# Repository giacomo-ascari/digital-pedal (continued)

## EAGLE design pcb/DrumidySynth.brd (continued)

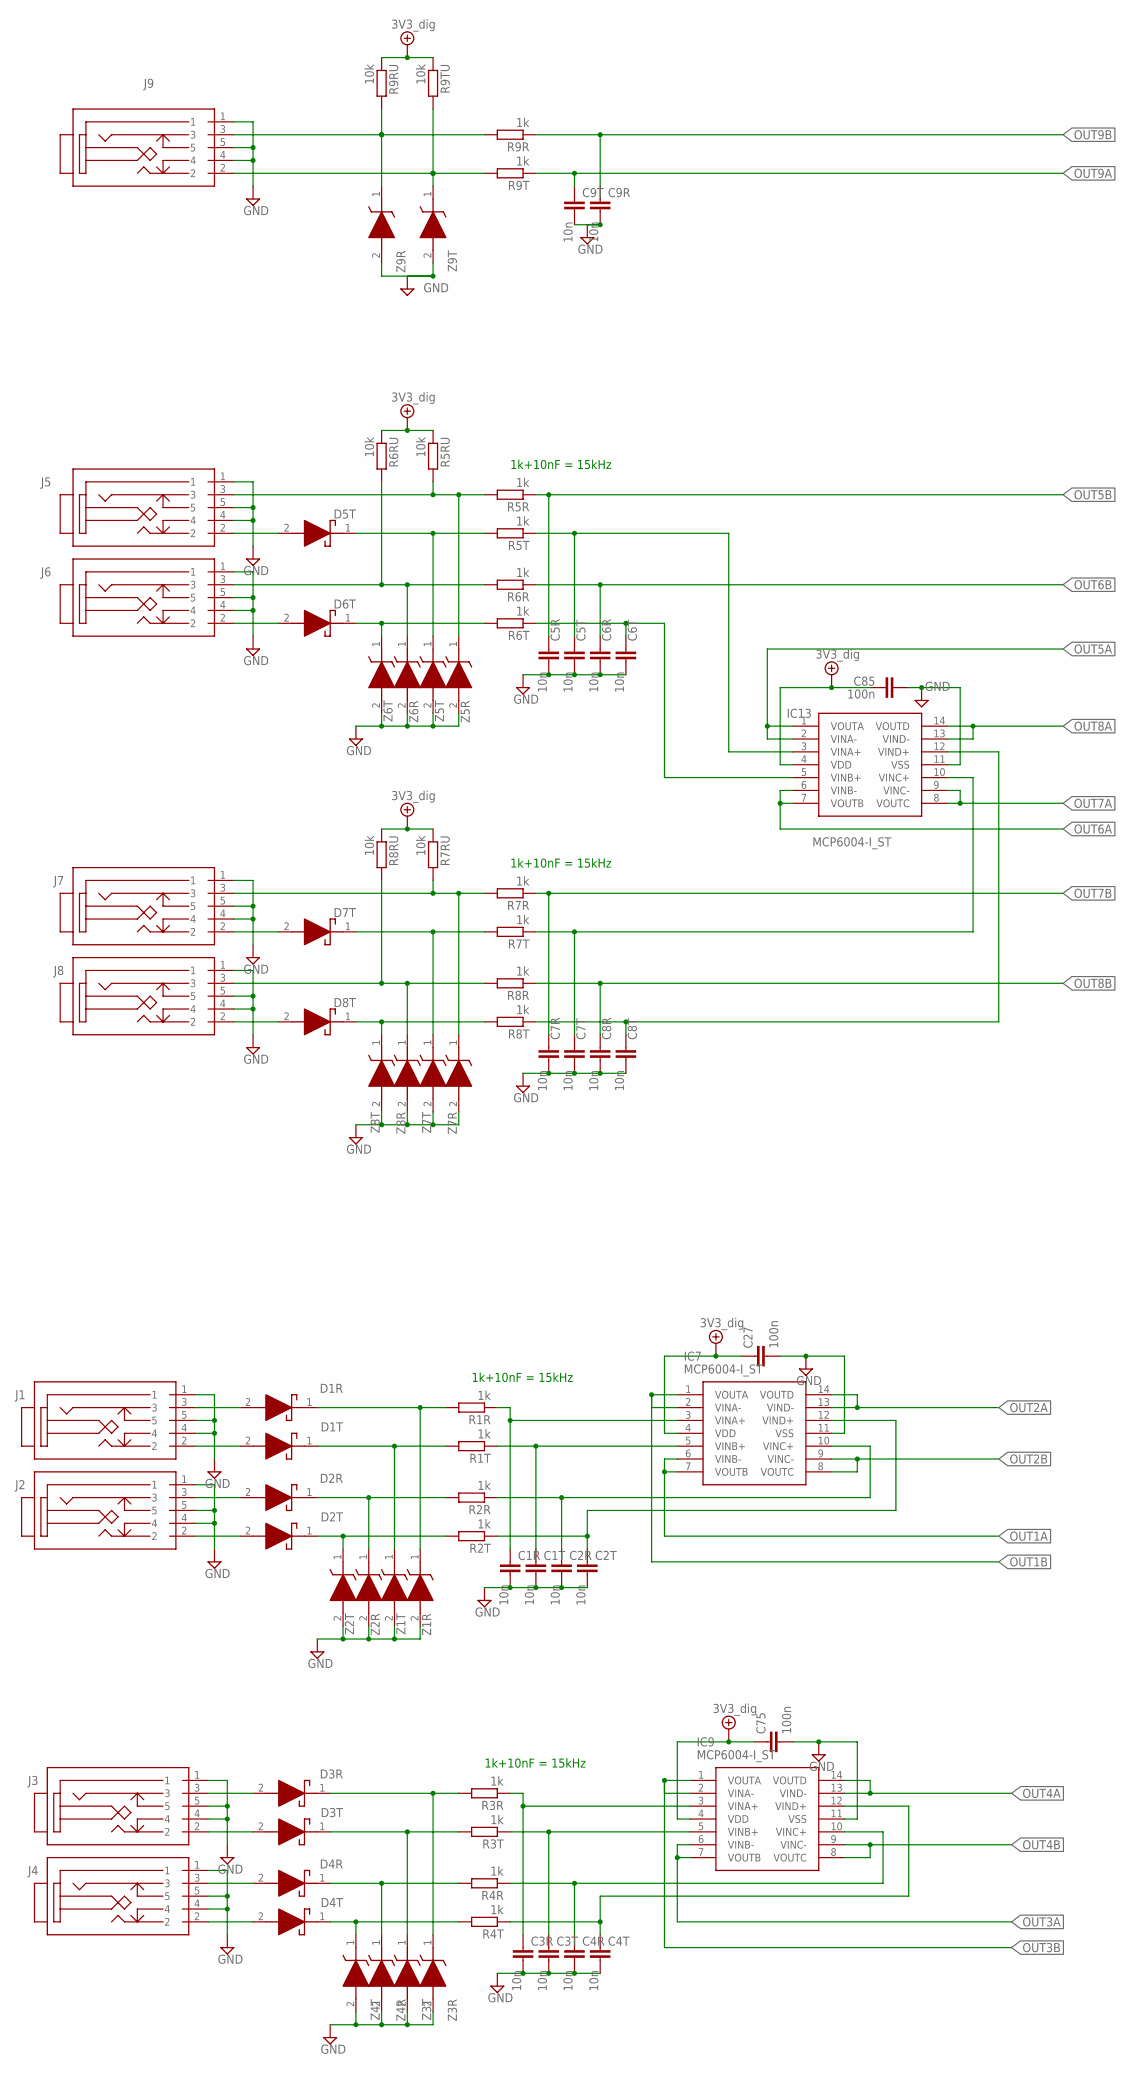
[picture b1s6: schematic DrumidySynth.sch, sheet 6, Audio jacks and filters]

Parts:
C1R, C1T, C2R, C2T, C3R, C3T, C4R, C4T, C5R, C5T, C6R, C6T, C7R, C7T, C8R, C8T, C9R, C9T: 10n; C0603K
C27, C75, C85: 100n; C0805
D1R, D1T, D2R, D2T, D3R, D3T, D4R, D4T, D5T, D6T, D7T, D8T: BAT54J,115; SODFL2512X80N
IC7, IC9, IC13: MCP6004-I_ST; SOP65P640X120-14N
J1, J2, J3, J4, J5, J6, J7, J8, J9: 35RAPC2AVN4
R1R, R1T, R2R, R2T, R3R, R3T, R4R, R4T, R5R, R5T, R6R, R6T, R7R, R7T, R8R, R8T, R9R, R9T: 1k; R0603
R5RU, R6RU, R7RU, R8RU, R9RU, R9TU: 10k; R0603
Z1R, Z1T, Z2R, Z2T, Z3R, Z3T, Z4R, Z4T, Z5R, Z5T, Z6R, Z6T, Z7R, Z7T, Z8R, Z8T, Z9R, Z9T: MM3Z3V3T1G; SOD2512X110N

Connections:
3V3D: C27.1, C75.1, C85.1, IC7.4 (VDD), IC9.4 (VDD), IC13.4 (VDD), R5RU.1, R6RU.1, R7RU.1, R8RU.1, R9RU.1, R9TU.1; also elsewhere on the board
GND: C1R.2, C1T.2, C2R.2, C2T.2, C3R.2, C3T.2, C4R.2, C4T.2, C5R.2, C5T.2, C6R.2, C6T.2, C7R.2, C7T.2, C8R.2, C8T.2, C9R.2, C9T.2, C27.2, C75.2, C85.2, IC7.11 (VSS), IC9.11 (VSS), IC13.11 (VSS), J1.1, J1.4, J1.5, J2.1, J2.4, J2.5, J3.1, J3.4, J3.5, J4.1, J4.4, J4.5, J5.1, J5.4, J5.5, J6.1, J6.4, J6.5, J7.1, J7.4, J7.5, J8.1, J8.4, J8.5, J9.1, J9.4, J9.5, Z1R.2 (A), Z1T.2 (A), Z2R.2 (A), Z2T.2 (A), Z3R.2 (A), Z3T.2 (A), Z4R.2 (A), Z4T.2 (A), Z5R.2 (A), Z5T.2 (A), Z6R.2 (A), Z6T.2 (A), Z7R.2 (A), Z7T.2 (A), Z8R.2 (A), Z8T.2 (A), Z9R.2 (A), Z9T.2 (A); also elsewhere on the board
IN0A: C1R.1, IC7.3 (VINA+), R1R.1
IN0A2: C3R.1, IC9.3 (VINA+), R3R.1
IN0B: C1T.1, IC7.5 (VINB+), R1T.1
IN0B1: C7T.1, IC13.10 (VINC+), R7T.1
IN0B2: C3T.1, IC9.5 (VINB+), R3T.1
IN0B4: C5T.1, IC13.3 (VINA+), R5T.1
IN1A: C2R.1, IC7.10 (VINC+), R2R.1
IN1A2: C4R.1, IC9.10 (VINC+), R4R.1
IN1B: C2T.1, IC7.12 (VIND+), R2T.1
IN1B1: C8T.1, IC13.12 (VIND+), R8T.1
IN1B2: C4T.1, IC9.12 (VIND+), R4T.1
unnamed: J7.3, R7R.2, R7RU.2, Z7R.1 (K)
unnamed: D7T.2 (A), J7.2
unnamed: J8.3, R8R.2, R8RU.2, Z8R.1 (K)
unnamed: D8T.2 (A), J8.2
unnamed: D1R.2 (A), J1.3
unnamed: D1T.2 (A), J1.2
unnamed: D2R.2 (A), J2.3
unnamed: D2T.2 (A), J2.2
unnamed: D1R.1 (K), R1R.2, Z1R.1 (K)
unnamed: D1T.1 (K), R1T.2, Z1T.1 (K)
unnamed: D2R.1 (K), R2R.2, Z2R.1 (K)
unnamed: D2T.1 (K), R2T.2, Z2T.1 (K)
unnamed: D7T.1 (K), R7T.2, Z7T.1 (K)
unnamed: D8T.1 (K), R8T.2, Z8T.1 (K)
unnamed: D3R.2 (A), J3.3
unnamed: D3T.2 (A), J3.2
unnamed: D4R.2 (A), J4.3
unnamed: D4T.2 (A), J4.2
unnamed: D3R.1 (K), R3R.2, Z3R.1 (K)
unnamed: D3T.1 (K), R3T.2, Z3T.1 (K)
unnamed: D4R.1 (K), R4R.2, Z4R.1 (K)
unnamed: D4T.1 (K), R4T.2, Z4T.1 (K)
unnamed: J9.3, R9R.2, R9RU.2, Z9R.1 (K)
unnamed: C6T.1, IC13.5 (VINB+), R6T.1
unnamed: J9.2, R9T.2, R9TU.2, Z9T.1 (K)
unnamed: J5.3, R5R.2, R5RU.2, Z5R.1 (K)
unnamed: D5T.2 (A), J5.2
unnamed: J6.3, R6R.2, R6RU.2, Z6R.1 (K)
unnamed: D6T.2 (A), J6.2
unnamed: D5T.1 (K), R5T.2, Z5T.1 (K)
unnamed: D6T.1 (K), R6T.2, Z6T.1 (K)
OUT1A: IC7.6 (VINB-), IC7.7 (VOUTB); also elsewhere on the board
OUT1B: IC7.1 (VOUTA), IC7.2 (VINA-); also elsewhere on the board
OUT2A: IC7.13 (VIND-), IC7.14 (VOUTD); also elsewhere on the board
OUT2B: IC7.8 (VOUTC), IC7.9 (VINC-); also elsewhere on the board
OUT3A: IC9.6 (VINB-), IC9.7 (VOUTB); also elsewhere on the board
OUT3B: IC9.1 (VOUTA), IC9.2 (VINA-); also elsewhere on the board
OUT4A: IC9.13 (VIND-), IC9.14 (VOUTD); also elsewhere on the board
OUT4B: IC9.8 (VOUTC), IC9.9 (VINC-); also elsewhere on the board
OUT5A: IC13.1 (VOUTA), IC13.2 (VINA-); also elsewhere on the board
OUT5B: C5R.1, R5R.1; also elsewhere on the board
OUT6A: IC13.6 (VINB-), IC13.7 (VOUTB); also elsewhere on the board
OUT6B: C6R.1, R6R.1; also elsewhere on the board
OUT7A: IC13.8 (VOUTC), IC13.9 (VINC-); also elsewhere on the board
OUT7B: C7R.1, R7R.1; also elsewhere on the board
OUT8A: IC13.13 (VIND-), IC13.14 (VOUTD); also elsewhere on the board
OUT8B: C8R.1, R8R.1; also elsewhere on the board
OUT9A: C9T.1, R9T.1; also elsewhere on the board
OUT9B: C9R.1, R9R.1; also elsewhere on the board

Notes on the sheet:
1k+10nF = 15kHz

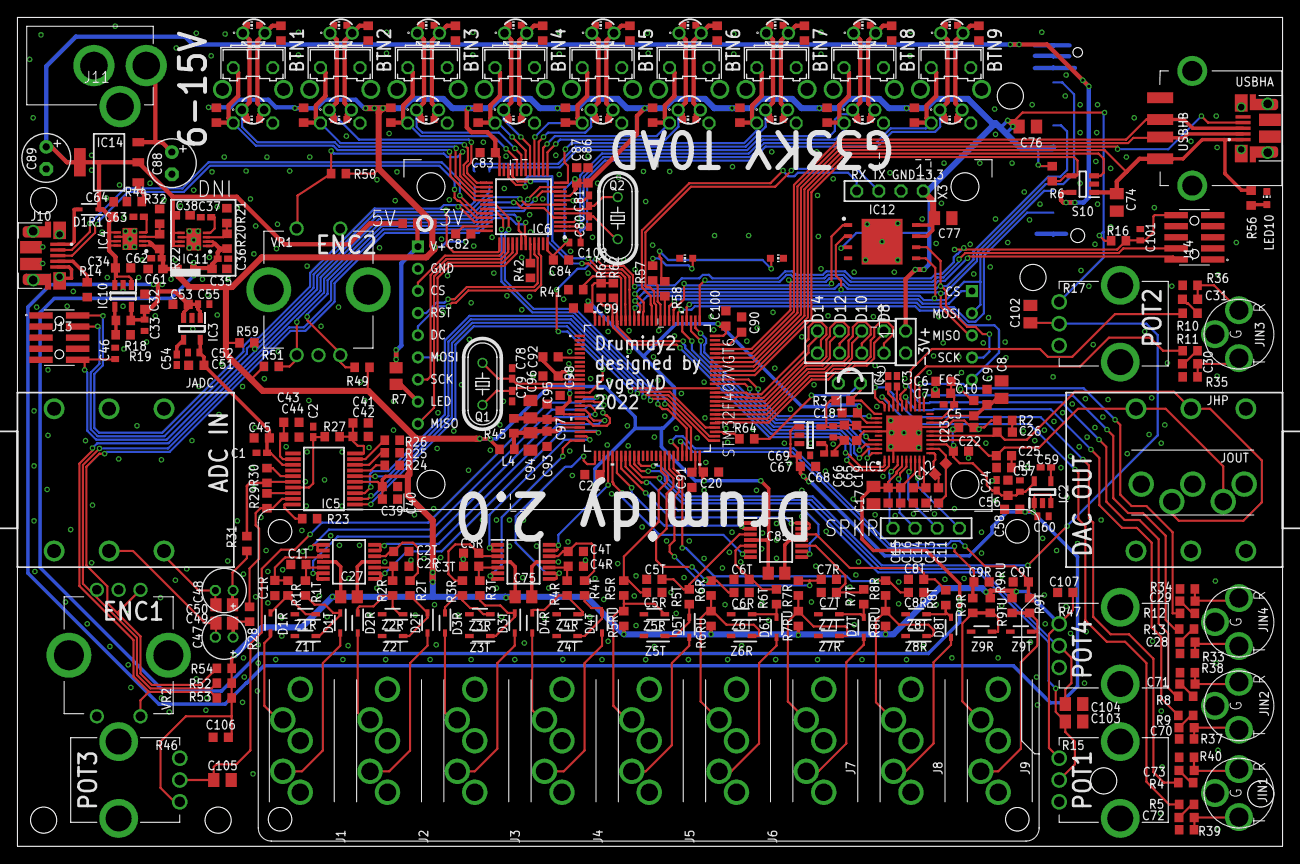
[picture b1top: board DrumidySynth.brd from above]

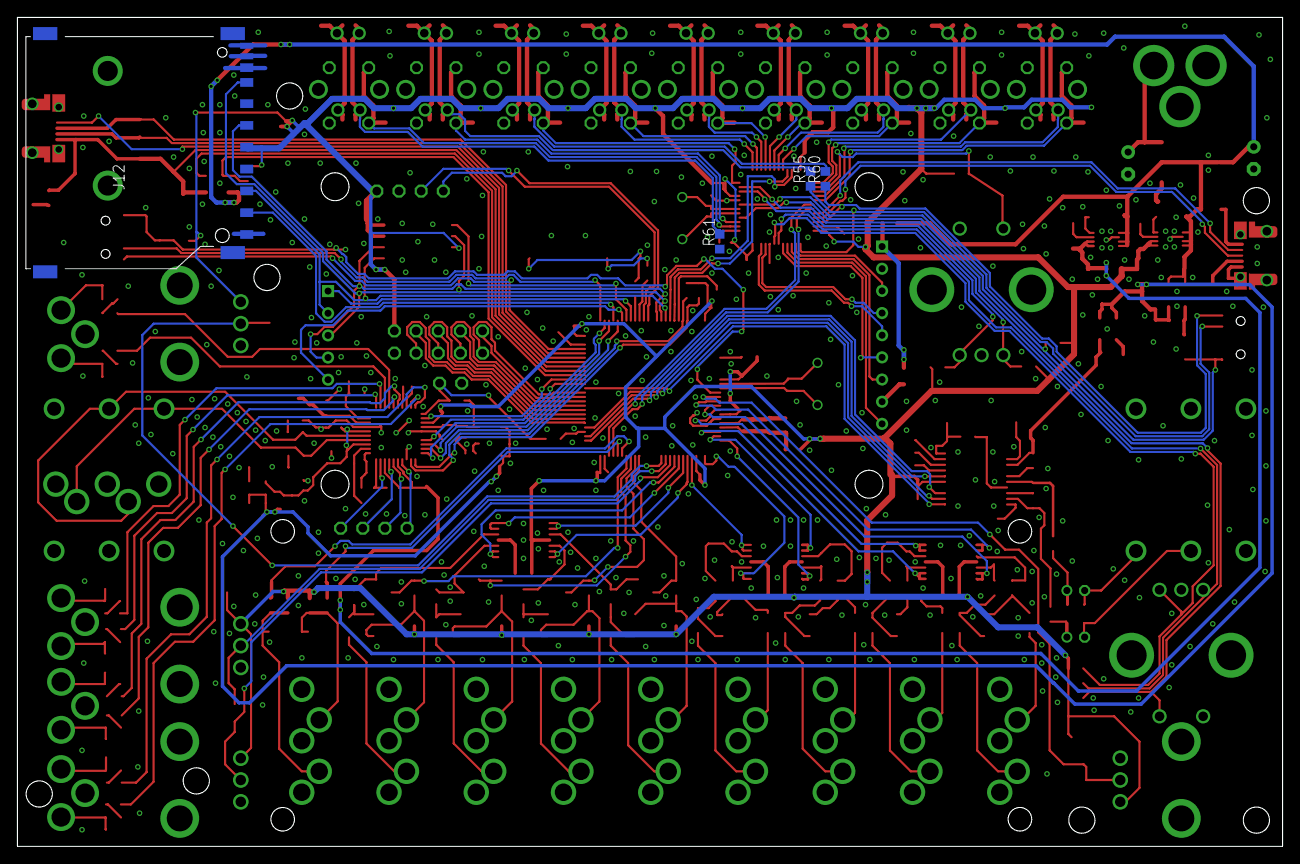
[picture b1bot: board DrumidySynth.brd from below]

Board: 2 copper layers, 145.0 x 95.0 mm, 363 parts (4 on the bottom side), 244 nets.

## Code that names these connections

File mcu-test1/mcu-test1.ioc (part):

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Mcu.Name=STM32F407V(E-G)Tx
Mcu.Package=LQFP100
Mcu.UserName=STM32F407VGTx
PA0-WKUP.GPIOParameters=GPIO_Label
PA0-WKUP.GPIO_Label=Btn0
PA0-WKUP.Signal=GPIO_Input
PA1.GPIOParameters=GPIO_Label
PA1.GPIO_Label=EPD_RST
PA1.Signal=GPIO_Output
PA11.GPIOParameters=GPIO_Speed
PA11.GPIO_Speed=GPIO_SPEED_FREQ_LOW
PA11.Mode=Host_Only
PA11.Signal=USB_OTG_FS_DM
PA12.GPIOParameters=GPIO_Speed
PA12.GPIO_Speed=GPIO_SPEED_FREQ_LOW
PA12.Mode=Host_Only
PA12.Signal=USB_OTG_FS_DP
PA13.Mode=Serial_Wire
PA13.Signal=SYS_JTMS-SWDIO
PA14.Mode=Serial_Wire
PA14.Signal=SYS_JTCK-SWCLK
PA2.GPIOParameters=GPIO_Label
PA2.GPIO_Label=EPD_DC
PA2.Signal=GPIO_Output
PA3.GPIOParameters=GPIO_Label
PA3.GPIO_Label=EPD_BUSY
PA3.Signal=GPIO_Input
PA4.GPIOParameters=GPIO_Speed
PA4.GPIO_Speed=GPIO_SPEED_FREQ_MEDIUM
PA4.Mode=Half_Duplex_Master
PA4.Signal=I2S3_WS
PA5.Mode=Simplex_Bidirectional_Master
PA5.Signal=SPI1_SCK
PA6.GPIOParameters=PinState,GPIO_Label
PA6.GPIO_Label=EPD_CS
PA6.PinState=GPIO_PIN_RESET
PA6.Signal=GPIO_Output
PA7.Mode=Simplex_Bidirectional_Master
PA7.Signal=SPI1_MOSI
PA9.Mode=Activate_VBUS
PA9.Signal=USB_OTG_FS_VBUS
PB11.GPIOParameters=GPIO_PuPd,GPIO_Label
PB11.GPIO_Label=Btn3
PB11.GPIO_PuPd=GPIO_PULLUP
PB11.Signal=GPIO_Input
PB12.GPIOParameters=GPIO_Speed
PB12.GPIO_Speed=GPIO_SPEED_FREQ_MEDIUM
PB12.Mode=Half_Duplex_Master
PB12.Signal=I2S2_WS
PB13.GPIOParameters=GPIO_Speed
PB13.GPIO_Speed=GPIO_SPEED_FREQ_MEDIUM
PB13.Mode=Half_Duplex_Master
PB13.Signal=I2S2_CK
PB14.GPIOParameters=GPIO_PuPd,GPIO_Label
PB14.GPIO_Label=Btn2
PB14.GPIO_PuPd=GPIO_PULLUP
PB14.Signal=GPIO_Input
PB15.GPIOParameters=GPIO_Speed
PB15.GPIO_Speed=GPIO_SPEED_FREQ_MEDIUM
PB15.Mode=Half_Duplex_Master
PB15.Signal=I2S2_SD
PB6.Mode=I2C
PB6.Signal=I2C1_SCL
PB9.Mode=I2C
PB9.Signal=I2C1_SDA
PC0.GPIOParameters=PinState,GPIO_Label
PC0.GPIO_Label=OtgPower
PC0.PinState=GPIO_PIN_RESET
PC0.Signal=GPIO_Output
PC10.GPIOParameters=GPIO_Speed
PC10.GPIO_Speed=GPIO_SPEED_FREQ_MEDIUM
PC10.Mode=Half_Duplex_Master
PC10.Signal=I2S3_CK
PC12.GPIOParameters=GPIO_Speed
PC12.GPIO_Speed=GPIO_SPEED_FREQ_MEDIUM
PC12.Mode=Half_Duplex_Master
PC12.Signal=I2S3_SD
PC2.GPIOParameters=GPIO_Label
PC2.GPIO_Label=EncB
PC2.Signal=GPIO_Input
PC3.GPIOParameters=GPIO_Label
PC3.GPIO_Label=EncA
PC3.Signal=GPIO_Input
PC6.GPIOParameters=GPIO_Speed
PC6.GPIO_Speed=GPIO_SPEED_FREQ_MEDIUM
PC6.Mode=Master_Clock_Activated
PC6.Signal=I2S2_MCK
PC7.GPIOParameters=GPIO_Speed
PC7.GPIO_Speed=GPIO_SPEED_FREQ_MEDIUM
PC7.Mode=Master_Clock_Activated
PC7.Signal=I2S3_MCK
PD12.GPIOParameters=GPIO_Label
PD12.GPIO_Label=Led1
PD12.Signal=GPIO_Output
PD13.GPIOParameters=GPIO_Label
PD13.GPIO_Label=Led2
PD13.Signal=GPIO_Output
PD14.GPIOParameters=GPIO_Label
PD14.GPIO_Label=Led3
PD14.Signal=GPIO_Output
PD15.GPIOParameters=PinState,GPIO_Label
PD15.GPIO_Label=Led4
PD15.PinState=GPIO_PIN_RESET
PD15.Signal=GPIO_Output
PD4.GPIOParameters=PinState,GPIO_Label
PD4.GPIO_Label=AudioPower
PD4.PinState=GPIO_PIN_SET
PD4.Signal=GPIO_Output
PD8.GPIOParameters=GPIO_PuPd,GPIO_Label
PD8.GPIO_Label=Btn1
PD8.GPIO_PuPd=GPIO_PULLUP
PD8.Signal=GPIO_Input
PH0-OSC_IN.Mode=HSE-External-Oscillator
PH0-OSC_IN.Signal=RCC_OSC_IN
PH1-OSC_OUT.Mode=HSE-External-Oscillator
PH1-OSC_OUT.Signal=RCC_OSC_OUT
RCC.HSE_VALUE=8000000
RCC.SYSCLKFreq_VALUE=168000000
RCC.SYSCLKSource=RCC_SYSCLKSOURCE_PLLCLK
board=custom

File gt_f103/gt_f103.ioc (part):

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Mcu.Name=STM32F103C(8-B)Tx
Mcu.Package=LQFP48
Mcu.UserName=STM32F103C8Tx
PA0-WKUP.GPIOParameters=GPIO_Label
PA0-WKUP.GPIO_Label=ENC2B
PA0-WKUP.Signal=GPIO_Input
PA1.GPIOParameters=GPIO_Label
PA1.GPIO_Label=ENC2A
PA1.Signal=GPIO_Input
PA13.Mode=Serial_Wire
PA13.Signal=SYS_JTMS-SWDIO
PA14.Mode=Serial_Wire
PA14.Signal=SYS_JTCK-SWCLK
PA15.GPIOParameters=GPIO_Label
PA15.GPIO_Label=LCD_CS
PA15.Signal=GPIO_Output
PA3.GPIOParameters=GPIO_Label
PA3.GPIO_Label=LD6
PA3.Signal=GPIO_Output
PA4.GPIOParameters=GPIO_Label,GPIO_ModeDefaultEXTI
PA4.GPIO_Label=BTN6
PA4.GPIO_ModeDefaultEXTI=GPIO_MODE_IT_FALLING
PA4.Signal=GPXTI4
PA5.GPIOParameters=GPIO_Label
PA5.GPIO_Label=LD5
PA5.Signal=GPIO_Output
PA6.GPIOParameters=GPIO_Label,GPIO_ModeDefaultEXTI
PA6.GPIO_Label=BTN5
PA6.GPIO_ModeDefaultEXTI=GPIO_MODE_IT_FALLING
PA6.Signal=GPXTI6
PA7.GPIOParameters=GPIO_Label
PA7.GPIO_Label=LD4
PA7.Signal=GPIO_Output
PA8.GPIOParameters=GPIO_Label,GPIO_ModeDefaultEXTI
PA8.GPIO_Label=BTN1
PA8.GPIO_ModeDefaultEXTI=GPIO_MODE_IT_FALLING
PA8.Signal=GPXTI8
PB0.GPIOParameters=GPIO_Label,GPIO_ModeDefaultEXTI
PB0.GPIO_Label=BTN4
PB0.GPIO_ModeDefaultEXTI=GPIO_MODE_IT_FALLING
PB0.Signal=GPXTI0
PB1.GPIOParameters=GPIO_Label
PB1.GPIO_Label=LD3
PB1.Signal=GPIO_Output
PB10.Mode=Asynchronous
PB10.Signal=USART3_TX
PB11.Mode=Asynchronous
PB11.Signal=USART3_RX
PB12.GPIOParameters=GPIO_Label
PB12.GPIO_Label=LD2
PB12.Signal=GPIO_Output
PB13.GPIOParameters=GPIO_Label,GPIO_ModeDefaultEXTI
PB13.GPIO_Label=BTN2
PB13.GPIO_ModeDefaultEXTI=GPIO_MODE_IT_FALLING
PB13.Signal=GPXTI13
PB14.GPIOParameters=GPIO_Label,GPIO_ModeDefaultEXTI
PB14.GPIO_Label=BTN_ENC2
PB14.GPIO_ModeDefaultEXTI=GPIO_MODE_IT_FALLING
PB14.Signal=GPXTI14
PB15.GPIOParameters=GPIO_Label
PB15.GPIO_Label=LD1
PB15.Signal=GPIO_Output
PB2.GPIOParameters=GPIO_Label,GPIO_ModeDefaultEXTI
PB2.GPIO_Label=BTN3
PB2.GPIO_ModeDefaultEXTI=GPIO_MODE_IT_FALLING
PB2.Signal=GPXTI2
PB3.Mode=Full_Duplex_Master
PB3.Signal=SPI1_SCK
PB4.Mode=Full_Duplex_Master
PB4.Signal=SPI1_MISO
PB5.Mode=Full_Duplex_Master
PB5.Signal=SPI1_MOSI
PB6.GPIOParameters=GPIO_Label
PB6.GPIO_Label=ENC1B
PB6.Signal=GPIO_Input
PB7.GPIOParameters=GPIO_Label
PB7.GPIO_Label=ENC1A
PB7.Signal=GPIO_Input
PB8.GPIOParameters=GPIO_Label
PB8.GPIO_Label=LCD_RST
PB8.Signal=GPIO_Output
PB9.GPIOParameters=GPIO_Label
PB9.GPIO_Label=LCD_DC
PB9.Signal=GPIO_Output
PC15-OSC32_OUT.GPIOParameters=GPIO_Label,GPIO_ModeDefaultEXTI
PC15-OSC32_OUT.GPIO_Label=BTN_ENC1
PC15-OSC32_OUT.GPIO_ModeDefaultEXTI=GPIO_MODE_IT_FALLING
PC15-OSC32_OUT.Signal=GPXTI15
PD0-OSC_IN.Mode=HSE-External-Oscillator
PD0-OSC_IN.Signal=RCC_OSC_IN
PD1-OSC_OUT.Mode=HSE-External-Oscillator
PD1-OSC_OUT.Signal=RCC_OSC_OUT
RCC.SYSCLKFreq_VALUE=72000000
RCC.SYSCLKSource=RCC_SYSCLKSOURCE_PLLCLK
board=custom

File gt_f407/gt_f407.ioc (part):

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Mcu.Name=STM32F407V(E-G)Tx
Mcu.Package=LQFP100
Mcu.UserName=STM32F407VGTx
PA11.Mode=Host_Only
PA11.Signal=USB_OTG_FS_DM
PA12.Mode=Host_Only
PA12.Signal=USB_OTG_FS_DP
PA13.Mode=Serial_Wire
PA13.Signal=SYS_JTMS-SWDIO
PA14.Mode=Serial_Wire
PA14.Signal=SYS_JTCK-SWCLK
PA15.Mode=Half_Duplex_Master
PA15.Signal=I2S3_WS
PA9.Mode=Activate_VBUS
PA9.Signal=USB_OTG_FS_VBUS
PB12.Mode=Half_Duplex_Master
PB12.Signal=I2S2_WS
PB13.Mode=Half_Duplex_Master
PB13.Signal=I2S2_CK
PB14.GPIOParameters=GPIO_Label
PB14.GPIO_Label=SPKRPower
PB14.Signal=GPIO_Output
PB15.Mode=Half_Duplex_Master
PB15.Signal=I2S2_SD
PB3.GPIOParameters=GPIO_Label
PB3.GPIO_Label=FLASH_SCK
PB3.Mode=Full_Duplex_Master
PB3.Signal=SPI1_SCK
PB4.GPIOParameters=GPIO_Label
PB4.GPIO_Label=FLASH_MISO
PB4.Mode=Full_Duplex_Master
PB4.Signal=SPI1_MISO
PB5.GPIOParameters=GPIO_Label
PB5.GPIO_Label=FLASH_MOSI
PB5.Mode=Full_Duplex_Master
PB5.Signal=SPI1_MOSI
PB6.Mode=Asynchronous
PB6.Signal=USART1_TX
PB7.Mode=Asynchronous
PB7.Signal=USART1_RX
PB8.Mode=I2C
PB8.Signal=I2C1_SCL
PB9.Mode=I2C
PB9.Signal=I2C1_SDA
PC0.GPIOParameters=GPIO_Label
PC0.GPIO_Label=USBPower
PC0.Signal=GPIO_Output
PC10.Mode=Half_Duplex_Master
PC10.Signal=I2S3_CK
PC12.Mode=Half_Duplex_Master
PC12.Signal=I2S3_SD
PC5.Signal=ADCx_IN15
PC6.Mode=Master_Clock_Activated
PC6.Signal=I2S2_MCK
PC7.Mode=Master_Clock_Activated
PC7.Signal=I2S3_MCK
PD1.GPIOParameters=GPIO_Label
PD1.GPIO_Label=FLASH_CS
PD1.Signal=GPIO_Output
PD3.GPIOParameters=GPIO_Label
PD3.GPIO_Label=LD1
PD3.Signal=GPIO_Output
PD4.GPIOParameters=GPIO_Label
PD4.GPIO_Label=LD2
PD4.Signal=GPIO_Output
PH0-OSC_IN.Mode=HSE-External-Oscillator
PH0-OSC_IN.Signal=RCC_OSC_IN
PH1-OSC_OUT.Mode=HSE-External-Oscillator
PH1-OSC_OUT.Signal=RCC_OSC_OUT
RCC.HSE_VALUE=8000000
RCC.SYSCLKFreq_VALUE=168000000
RCC.SYSCLKSource=RCC_SYSCLKSOURCE_PLLCLK
board=custom

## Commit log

2022-02-09 test
2022-04-10 update biblio
2022-05-27 stuff
2022-06-13 update on font
2022-07-03 aaaaaaaaaaaaaaaaaaaaaa
2022-07-28 major update
2022-08-15 sperente
2022-08-17 font update
2023-03-28 update (backup up for epd display)
2023-04-04 update (basic implementation of lcd done)
2023-04-13 update (checkpoint pedalboard)
2023-04-14 update (checkpoint for baker)
2023-04-17 update (db working)
2023-08-15 pre dk
